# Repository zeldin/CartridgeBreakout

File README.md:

Cartridge Breakout
==================

This is a PCB to break out the signals of a 44-contact 2.54 mm card edge
connector, as used in cartridges for the C64, to pin headers.  It was
designed for use with the Orange Cartridge, but can be used with any C64
cartridge, or even other compatible card edge devices.

The board can be used for testing, debugging and prototyping cartridges
and FPGA cartridge gateware and software.

Features
--------

- 40 of the 44 contacts are routed to individual pins compatible
  with IDC or Dupont wiring.

- The 4 corner contacts are instead connected to a ground plane
  which is available on 40 pins, one for each signal pin.

- There is a 5V power plane which can be used to inject power into
  contacts 2 and 3, or just one of them if so desired.

- There is a 5-signal JTAG/SWD breakout from a 2x5 1.27 mm pin header,
  as a wired side channel to the cartridge.

- There is also a 2-signal UART breakout from a 1x3 1.27 mm pin header,
  likewise a wired side channel.

- There are two LEDs which can be controlled with a single pin, to support
  semi-automated testing setups.

Documentation
-------------

**[Building instructions](doc/Building.md)**  
**[User manual](doc/UserManual.md)**

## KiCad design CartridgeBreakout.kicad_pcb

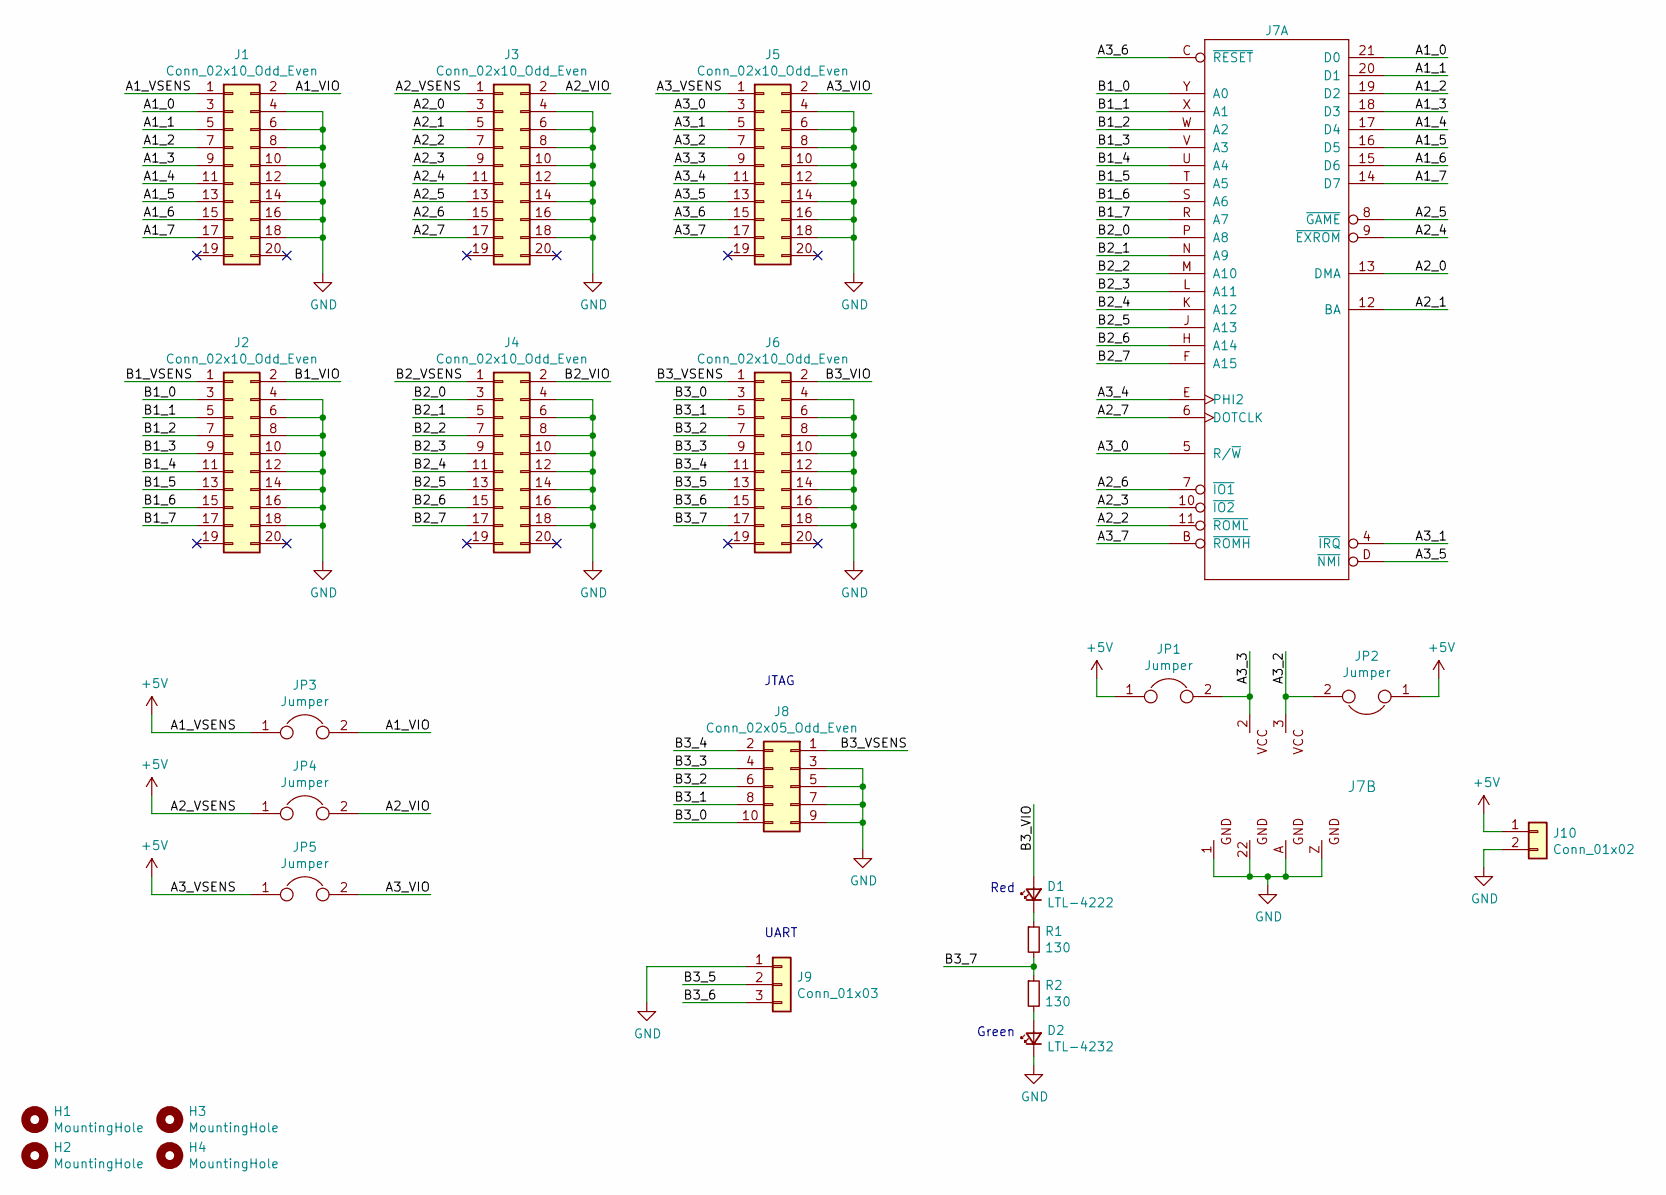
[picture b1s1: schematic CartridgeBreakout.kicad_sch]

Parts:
D1: LTL-4222; LED_D3.0mm; Mouser SKU 859-LTL-4222
D2: LTL-4232; LED_D3.0mm; Mouser SKU 859-LTL-4232
H1, H2, H3, H4: MountingHole; MountingHole_3.2mm_M3
J1, J2, J3, J4, J5, J6: Conn_02x10_Odd_Even; IDC-Header_2x10_P2.54mm_Vertical; Mouser SKU 538-87834-2019
J7: EXPANSION_PORT_C64_EDGE; TE_5530843-4; Mouser SKU 571-5530843-4
J8: Conn_02x05_Odd_Even; FTSH-105-XX-X-DV; Mouser SKU 200-FTSH10501FDVKTR
J9: Conn_01x03; PinHeader_1x03_P1.27mm_Vertical_SMD_Pin1Right; Mouser SKU 855-M50-3630342
J10: Conn_01x02; 284512-2; Mouser SKU 571-284512-2
JP1, JP2, JP3, JP4, JP5: Jumper; PinHeader_1x02_P2.54mm_Vertical; Mouser SKU 538-22-28-4023
R1, R2: 130; R_0603_1608Metric_Pad0.98x0.95mm_HandSolder; Mouser SKU 603-AC0603JR-07130RL

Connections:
+5V: J1.1, J3.1, J5.1, J10.1, JP1.1, JP2.1, JP3.1, JP4.1, JP5.1
/A1_0: J1.3, J7.21 (D0)
/A1_1: J1.5, J7.20 (D1)
/A1_2: J1.7, J7.19 (D2)
/A1_3: J1.9, J7.18 (D3)
/A1_4: J1.11, J7.17 (D4)
/A1_5: J1.13, J7.16 (D5)
/A1_6: J1.15, J7.15 (D6)
/A1_7: J1.17, J7.14 (D7)
/A1_VIO: J1.2, JP3.2
/A2_0: J3.3, J7.13 (DMA)
/A2_1: J3.5, J7.12 (BA)
/A2_2: J3.7, J7.11 (~ROML)
/A2_3: J3.9, J7.10 (~IO2)
/A2_4: J3.11, J7.9 (~EXROM)
/A2_5: J3.13, J7.8 (~GAME)
/A2_6: J3.15, J7.7 (~IO1)
/A2_7: J3.17, J7.6 (DOTCLK)
/A2_VIO: J3.2, JP4.2
/A3_0: J5.3, J7.5 (R/~W)
/A3_1: J5.5, J7.4 (~IRQ)
/A3_2: J5.7, J7.3 (VCC@1), JP2.2
/A3_3: J5.9, J7.2 (VCC), JP1.2
/A3_4: J5.11, J7.E (PHI2)
/A3_5: J5.13, J7.D (~NMI)
/A3_6: J5.15, J7.C (~RESET)
/A3_7: J5.17, J7.B (~ROMH)
/A3_VIO: J5.2, JP5.2
/B1_0: J2.3, J7.Y (A0)
/B1_1: J2.5, J7.X (A1)
/B1_2: J2.7, J7.W (A2)
/B1_3: J2.9, J7.V (A3)
/B1_4: J2.11, J7.U (A4)
/B1_5: J2.13, J7.T (A5)
/B1_6: J2.15, J7.S (A6)
/B1_7: J2.17, J7.R (A7)
/B1_VIO: J2.2
/B1_VSENS: J2.1
/B2_0: J4.3, J7.P (A8)
/B2_1: J4.5, J7.N (A9)
/B2_2: J4.7, J7.M (A10)
/B2_3: J4.9, J7.L (A11)
/B2_4: J4.11, J7.K (A12)
/B2_5: J4.13, J7.J (A13)
/B2_6: J4.15, J7.H (A14)
/B2_7: J4.17, J7.F (A15)
/B2_VIO: J4.2
/B2_VSENS: J4.1
/B3_0: J6.3, J8.10
/B3_1: J6.5, J8.8
/B3_2: J6.7, J8.6
/B3_3: J6.9, J8.4
/B3_4: J6.11, J8.2
/B3_5: J6.13, J9.2
/B3_6: J6.15, J9.3
/B3_7: J6.17, R1.2, R2.1
/B3_VIO: D1.2 (A), J6.2
/B3_VSENS: J6.1, J8.1
GND: D2.1 (K), J1.4, J1.6, J1.8, J1.10, J1.12, J1.14, J1.16, J1.18, J2.4, J2.6, J2.8, J2.10, J2.12, J2.14, J2.16, J2.18, J3.4, J3.6, J3.8, J3.10, J3.12, J3.14, J3.16, J3.18, J4.4, J4.6, J4.8, J4.10, J4.12, J4.14, J4.16, J4.18, J5.4, J5.6, J5.8, J5.10, J5.12, J5.14, J5.16, J5.18, J6.4, J6.6, J6.8, J6.10, J6.12, J6.14, J6.16, J6.18, J7.1 (GND), J7.22 (GND@1), J7.A (GND@2), J7.Z (GND@3), J8.3, J8.5, J8.7, J8.9, J9.1, J10.2
unnamed: D1.1 (K), R1.1
unnamed: D2.2 (A), R2.2

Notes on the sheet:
Green
Red
UART
JTAG

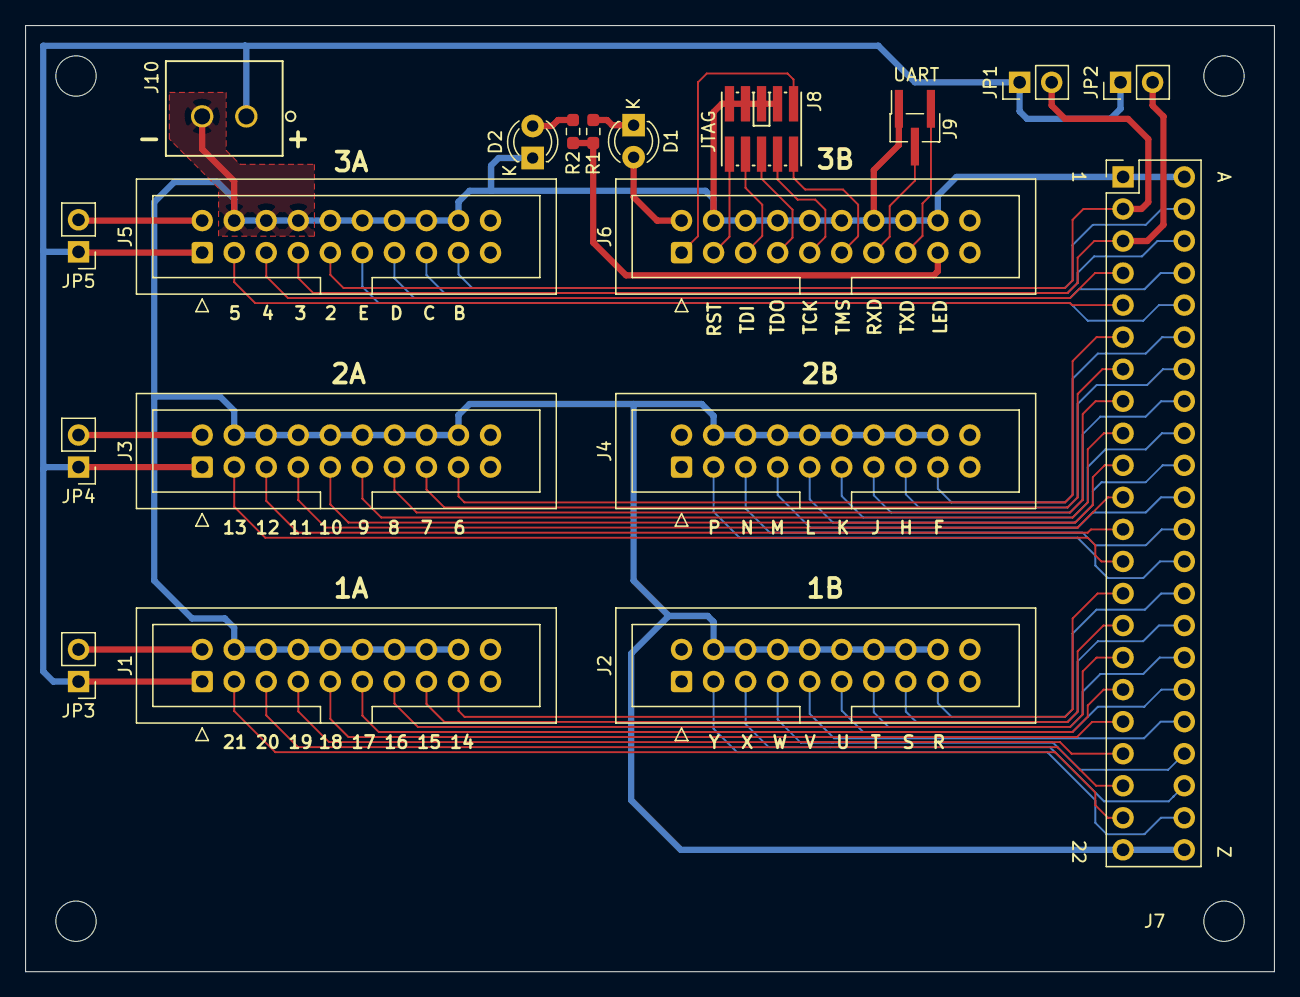
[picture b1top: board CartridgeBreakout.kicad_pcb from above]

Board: 2 copper layers, 99.0 x 75.0 mm, 23 parts (0 on the bottom side), 57 nets.

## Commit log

2022-02-03 Ignore FP info cache
2022-02-05 Add some documentation
2022-02-05 Add a permissive license
2022-02-05 Converted to KiCAD 6 format
2022-02-12 Add building instructions
2022-02-12 Replace STEP models with VRML
2022-02-13 Update rendered picture
